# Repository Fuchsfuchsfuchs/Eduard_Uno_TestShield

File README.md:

# Eduard_Uno_TestShield
A testprogram for the breakout arduino uno on the back of the eduard robot

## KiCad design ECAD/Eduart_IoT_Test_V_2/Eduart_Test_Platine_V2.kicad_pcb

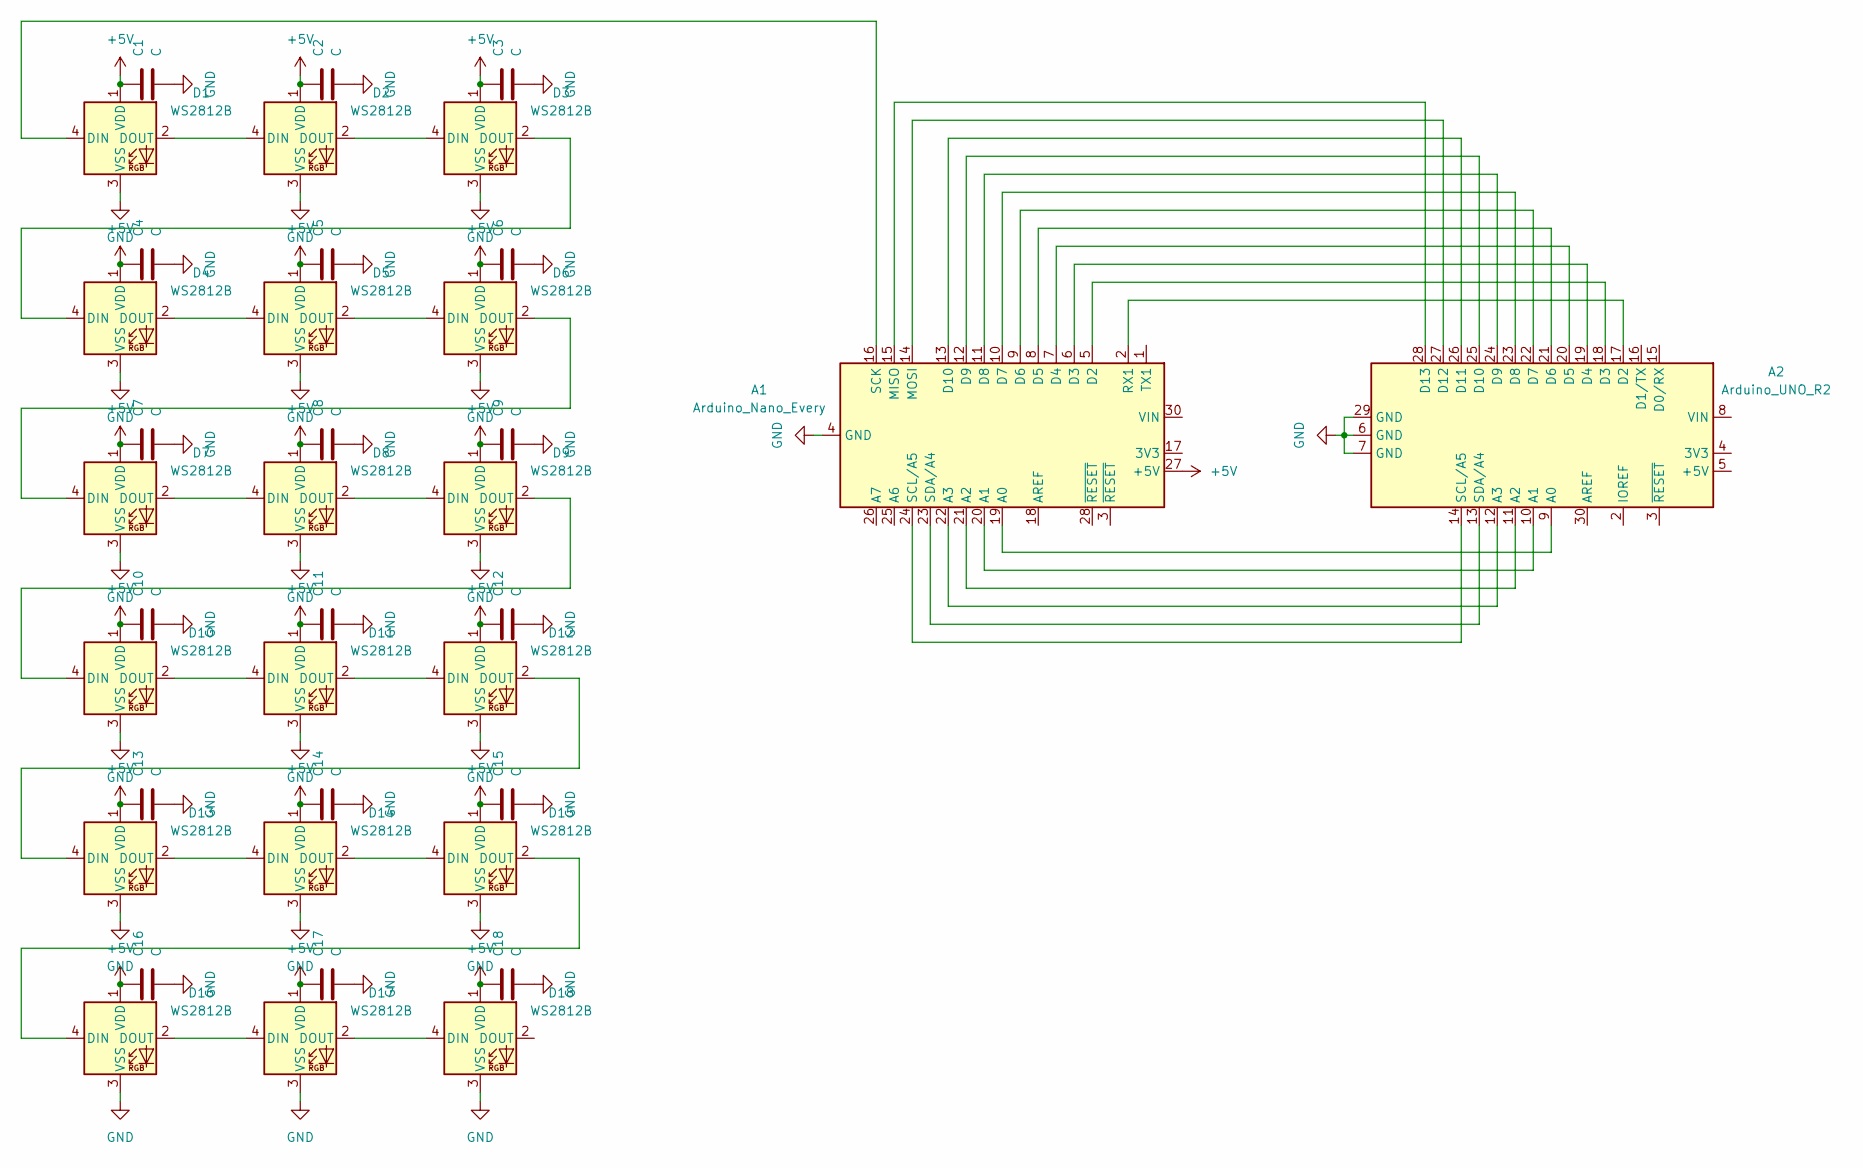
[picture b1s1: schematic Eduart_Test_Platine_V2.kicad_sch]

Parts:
A1: Arduino_Nano_Every; Arduino_Nano
A2: Arduino_UNO_R2
C1, C2, C3, C4, C5, C6, C7, C8, C9, C10, C11, C12, C13, C14, C15, C16, C17, C18: C; C_0201_0603Metric_Pad0.64x0.40mm_HandSolder
D1, D2, D3, D4, D5, D6, D7, D8, D9, D10, D11, D12, D13, D14, D15, D16, D17, D18: WS2812B; LED_WS2812B_PLCC4_5.0x5.0mm_P3.2mm

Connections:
+5V: A1.27 (+5V), C1.1, C2.1, C3.1, C4.1, C5.1, C6.1, C7.1, C8.1, C9.1, C10.1, C11.1, C12.1, C13.1, C14.1, C15.1, C16.1, C17.1, C18.1, D1.1 (VDD), D2.1 (VDD), D3.1 (VDD), D4.1 (VDD), D5.1 (VDD), D6.1 (VDD), D7.1 (VDD), D8.1 (VDD), D9.1 (VDD), D10.1 (VDD), D11.1 (VDD), D12.1 (VDD), D13.1 (VDD), D14.1 (VDD), D15.1 (VDD), D16.1 (VDD), D17.1 (VDD), D18.1 (VDD)
GND: A1.4 (GND), A1.29 (GND), A2.6 (GND), A2.7 (GND), A2.29 (GND), C1.2, C2.2, C3.2, C4.2, C5.2, C6.2, C7.2, C8.2, C9.2, C10.2, C11.2, C12.2, C13.2, C14.2, C15.2, C16.2, C17.2, C18.2, D1.3 (VSS), D2.3 (VSS), D3.3 (VSS), D4.3 (VSS), D5.3 (VSS), D6.3 (VSS), D7.3 (VSS), D8.3 (VSS), D9.3 (VSS), D10.3 (VSS), D11.3 (VSS), D12.3 (VSS), D13.3 (VSS), D14.3 (VSS), D15.3 (VSS), D16.3 (VSS), D17.3 (VSS), D18.3 (VSS)
unnamed: A1.19 (A0), A2.9 (A0)
unnamed: A1.20 (A1), A2.10 (A1)
unnamed: A1.21 (A2), A2.11 (A2)
unnamed: A1.22 (A3), A2.12 (A3)
unnamed: A1.5 (D2), A2.18 (D3)
unnamed: A1.6 (D3), A2.19 (D4)
unnamed: A1.7 (D4), A2.20 (D5)
unnamed: A1.8 (D5), A2.21 (D6)
unnamed: A1.9 (D6), A2.22 (D7)
unnamed: A1.10 (D7), A2.23 (D8)
unnamed: A1.11 (D8), A2.24 (D9)
unnamed: A1.12 (D9), A2.25 (D10)
unnamed: A1.13 (D10), A2.26 (D11)
unnamed: A1.15 (MISO), A2.28 (D13)
unnamed: A1.14 (MOSI), A2.27 (D12)
unnamed: A1.2 (RX1), A2.17 (D2)
unnamed: A1.16 (SCK), D1.4 (DIN)
unnamed: A1.24 (SCL/A5), A2.14 (SCL/A5)
unnamed: A1.23 (SDA/A4), A2.13 (SDA/A4)
unnamed: D1.2 (DOUT), D2.4 (DIN)
unnamed: D2.2 (DOUT), D3.4 (DIN)
unnamed: D3.2 (DOUT), D4.4 (DIN)
unnamed: D4.2 (DOUT), D5.4 (DIN)
unnamed: D5.2 (DOUT), D6.4 (DIN)
unnamed: D6.2 (DOUT), D7.4 (DIN)
unnamed: D7.2 (DOUT), D8.4 (DIN)
unnamed: D8.2 (DOUT), D9.4 (DIN)
unnamed: D9.2 (DOUT), D10.4 (DIN)
unnamed: D10.2 (DOUT), D11.4 (DIN)
unnamed: D11.2 (DOUT), D12.4 (DIN)
unnamed: D12.2 (DOUT), D13.4 (DIN)
unnamed: D13.2 (DOUT), D14.4 (DIN)
unnamed: D14.2 (DOUT), D15.4 (DIN)
unnamed: D15.2 (DOUT), D16.4 (DIN)
unnamed: D16.2 (DOUT), D17.4 (DIN)
unnamed: D17.2 (DOUT), D18.4 (DIN)

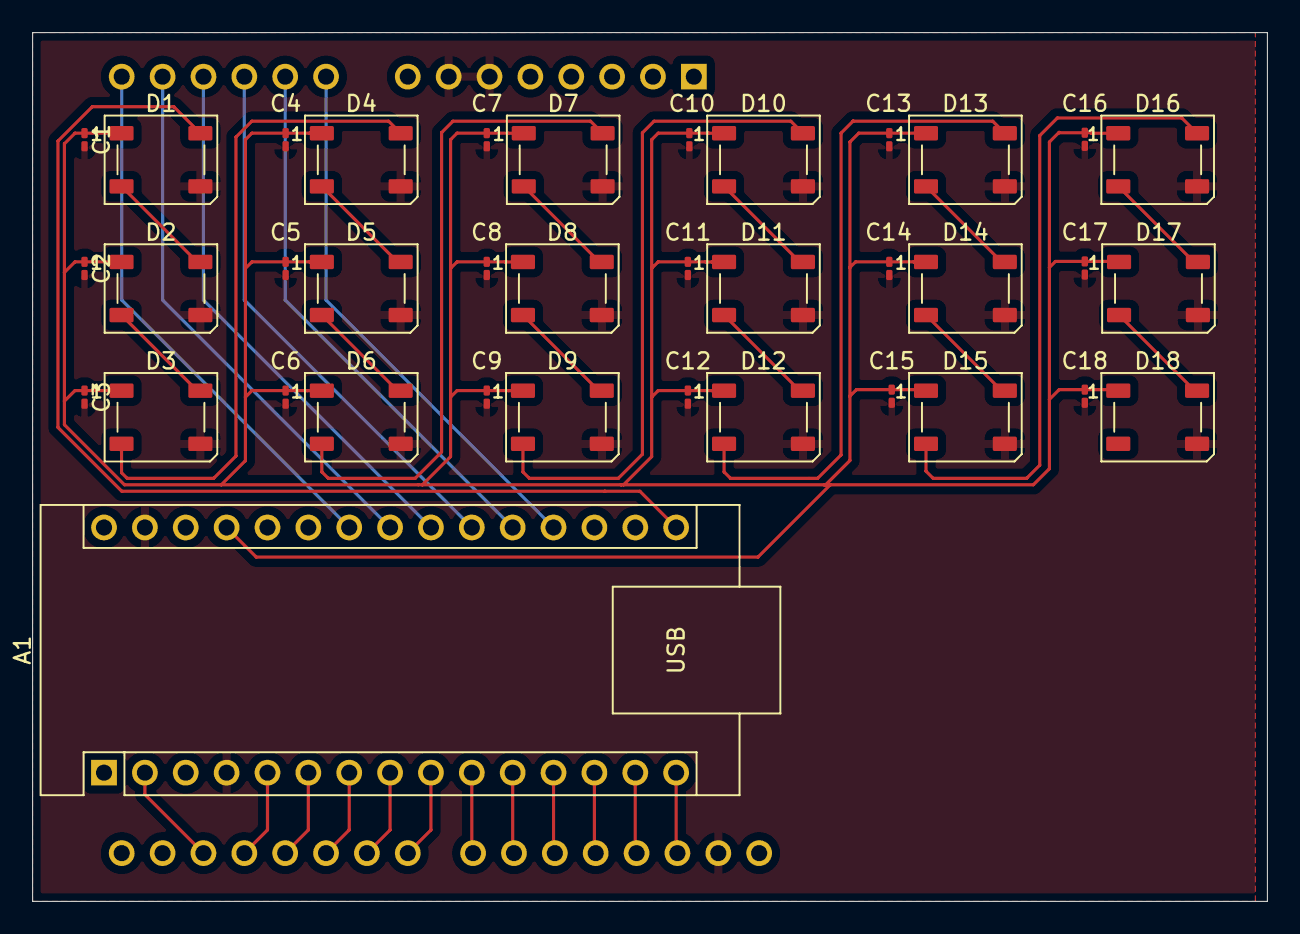
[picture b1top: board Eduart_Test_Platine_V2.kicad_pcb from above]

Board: 2 copper layers, 76.8 x 54.0 mm, 38 parts (1 on the bottom side), 38 nets.

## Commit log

2025-06-23 Rename .gitignore to .gitignore
2025-06-25 Add files via upload
    Decoupling Capacitors better placement.
    Silkscreen cleanup.
